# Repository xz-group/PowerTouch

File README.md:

# PowerTouch

A Genetic Algorithm-based framework that can automatically generate `wired ghost touch attacks` given security objectives (e.g., types and locations of desired ghost touches).

## About this work

For more details, please refer to our **ICCAD'22** paper: [_PowerTouch: A Security Objective-Guided Automation Framework
for Generating Wired Ghost Touch Attacks on Touchscreens_](ICCAD2022_PowerTouch.pdf).

## Dependencies

### Software Dependencies

* Standard packages: `ctypes`, `numpy`, `re`, `datetime`, `pandas`, `warnings`, `matplotlib`, `statistics`, `time`

* Python Genetic Algorithm Library: [PyGAD](https://pygad.readthedocs.io/en/latest/)
  ```bash
  pip install pygad
  ```

* Android Debug Bridge (ADB): [Android SDK Platform Tools](https://developer.android.com/studio/releases/platform-tools).
  > Currently, the framework only supports Android devices. We will add support for iOS devices in the future.

* Clone this repository
  ```bash
  git clone https://github.com/xz-group/PowerTouch.git
  ```

### Hardware Dependencies

* `All-in-one USB instrument`: [Analog Discovery 2](https://digilent.com/shop/analog-discovery-2-100ms-s-usb-oscilloscope-logic-analyzer-and-variable-power-supply/) 
with [BNC Adapter board](https://digilent.com/shop/bnc-adapter-for-analog-discovery/).

  * Five instruments are implemented in Analog Discovery 2 for this framework: 
    * `oscilloscope`: to capture the TX excitation signal of the touchscreen and monitor the generated noise signal.
    * `waveform generator`: to generate the noise signal.
    * `pattern generator`: to generate digital control signals for the relays on the customized noise injection PCB.
    * `logic analyzer`: to monitor the above digital control signals.
    * `power supply`: to power the customized noise injection PCB.

* `High-voltage amplifier module`: we use [MX200 Piezo Driver](https://www.piezodrive.com/modules/mx200-high-performance-piezo-driver/) for this project.
  But any high-voltage amplifier module that can generate minimum 60Vpp signal with 500kHz bandwidth should work.
  >   The bandwidth of MX200 is 200KHz also. We extend the bandwidth to around 500KHz by calibrating the gain of the amplifier. See [here]() for details.

* Our `customized noise injection PCB`: source design files are available in [hardware](./hardware) folder.
  
  * The board is powered by 5V through `5V` and `GND` pins. 
  * It contains four RF relay ([9814-500 relay](https://www.digikey.com/en/products/detail/coto-technology/9814-05-00/586522)) channels: CH1, CH2, CH3, and CH4.
    * `CH1` is used to capture the TX excitation signal of the touchscreen. It is connected to the `SHIELD` of USB connector.
    * `CH2` is used to inject high-voltage noise signal to the touchscreen. It is connected to the `SHIELD` of USB connector.
    * `CH3` and `CH4` are used to charge the smartphone when conducting the experiments. They are connected to the `VBUS` and `VGND` of USB connector, respectively.
  * The relays are controlled through `EN_CH1`, `EN_CH2`, `EN_CH3`, `EN_CH4` pins, respectively. High enables (>=3.3V) the relays, and low disables the relays.
  * `CH1` and `CH2` are connected outside the PCB through `BNC` connectors. The `SMA` connectors. `SHIELD` is connected outside the PCB through `BNC` connectors. 

* `Power supply`: this is used to power the high-voltage amplifier module and charge the smartphone (if enable charging the phone feature). We use [Keithley 2231A-30-3 Triple-channel DC Power Supply](https://www.tek.com/en/products/keithley/dc-power-supplies/2220-2230-2231-series).

* `Metal sheet`: to be connected to the `EARTH` of the wall outlet. This is used to build the true ground plane for converting the noise from differential mode to common mode.
We use [this one](https://a.co/d/iU6o7kK) for this project.

## How to Use

Please refer to the example usage code in `PowerTouch/example_usage_code` folder for details.

## Citation

If you use this framework for your research, please cite our [ICCAD'22 paper](ICCAD2022_PowerTouch.pdf):

```
@inproceedings{zhu2022powertouch,
  title={PowerTouch: A Security Objective-Guided Automation Framework for Generating Wired Ghost Touch Attacks on Touchscreens},
  author={Zhu, Huifeng and Yu, Zhiyuan and Cao, Weidong and Zhang, Ning and Zhang, Xuan},
  booktitle={Proceedings of the 41st IEEE/ACM International Conference on Computer-Aided Design},
  pages={1--9},
  year={2022}
}
```

## Contact Information

If you have any questions regarding using this framework, please feel free to contact us at [zhuhuifeng@wustl.edu](mailto:zhuhuifeng@wustl.edu).

## Roadmap
- [ ] To be updated

## Version History

* 0.1
  * Initial Release

## License

This framework is licensed under the `GNU3` License - see the [LICENSE.md](LICENSE) file for details

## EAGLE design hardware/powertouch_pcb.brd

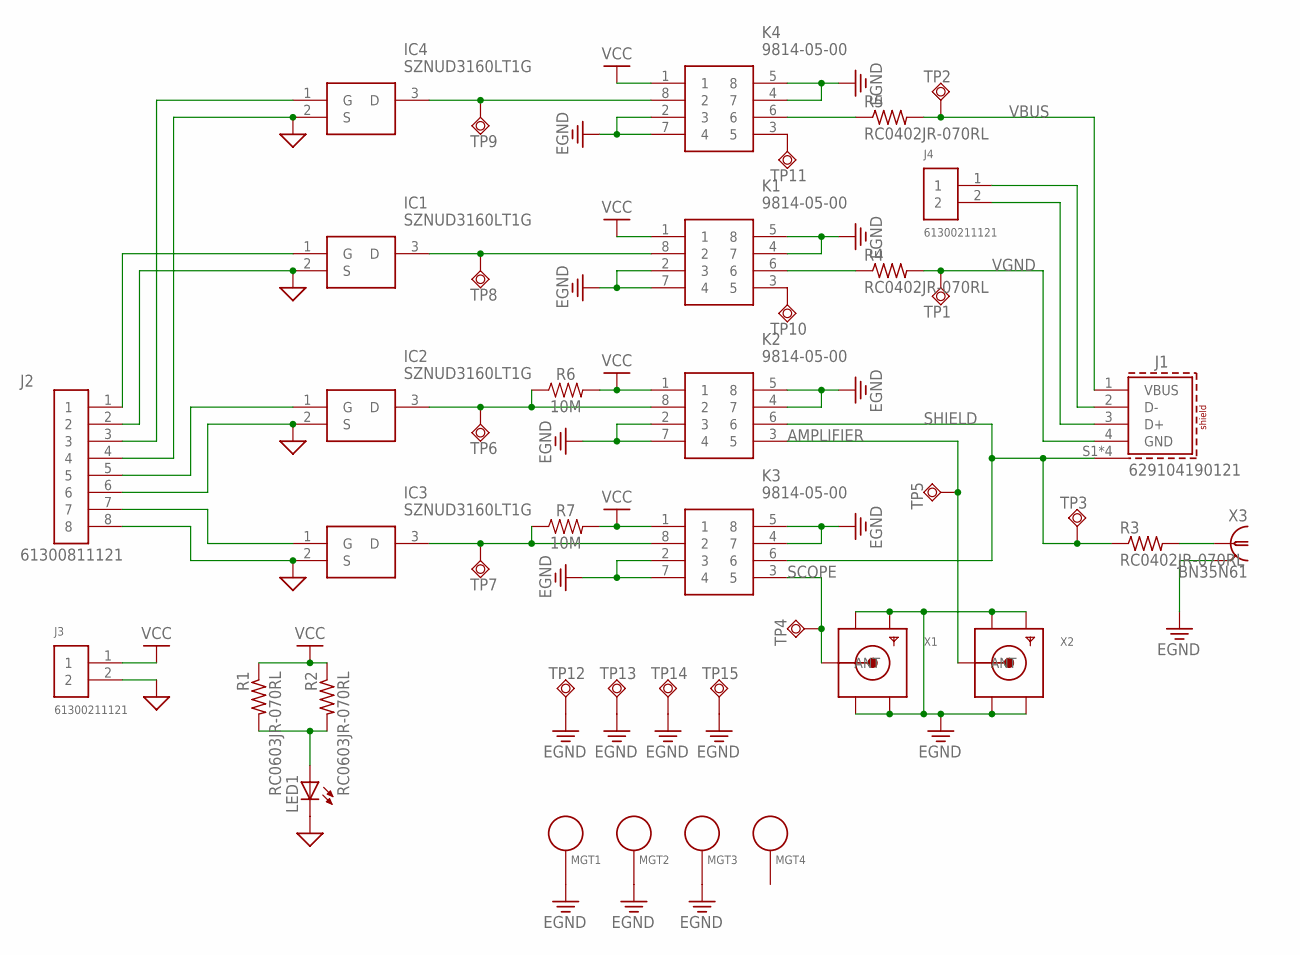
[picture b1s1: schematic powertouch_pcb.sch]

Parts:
IC1, IC2, IC3, IC4: SZNUD3160LT1G; SOT96P237X111-3N
J1: 629104190121
J2: 61300811121
J3, J4: 61300211121
K1, K2, K3, K4: 9814-05-00; SOP102P1295X457-8N
LED1: LEDCHIPLED_0603; CHIPLED_0603
MGT1, MGT2, MGT3, MGT4: BEAGLEBONEBLACK_MOUNTING_HOLE
R1, R2: RC0603JR-070RL; RES_0603
R3, R4, R5: RC0402JR-070RL; RES_0402
R6, R7: 10M; AXIAL-0.3
TP1, TP2, TP3, TP4, TP5, TP10, TP11, TP12, TP13, TP14, TP15: TESTPAD_TPSQPAD1-13; TESTPAD_P1-13
TP6, TP7, TP8, TP9: TESTPAD_TPSQTP07SQ; TESTPAD_TP07SQ
X1, X2: SMACONNECTOR_EDGE; SMA_EDGELAUNCH
X3: BN35N61; B35N61

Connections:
AMPLIFIER: K2.3 (5), TP5.TP, X2.P (ANT)
EGND: K1.2 (3), K1.4 (7), K1.5 (8), K1.7 (4), K2.2 (3), K2.4 (7), K2.5 (8), K2.7 (4), K3.2 (3), K3.4 (7), K3.5 (8), K3.7 (4), K4.2 (3), K4.4 (7), K4.5 (8), K4.7 (4), MGT1.P$1, MGT2.P$1, MGT3.P$1, TP12.TP, TP13.TP, TP14.TP, TP15.TP, X1.GND@1 (GND4), X1.GND@2 (GND3), X1.GND@3 (GND2), X1.GND@4 (GND1), X2.GND@1 (GND4), X2.GND@2 (GND3), X2.GND@3 (GND2), X2.GND@4 (GND1), X3.2, X3.3 (2), X3.4 (2), X3.5 (2)
GND: IC1.2 (S), IC2.2 (S), IC3.2 (S), IC4.2 (S), J2.2, J2.4, J2.6, J2.8, J3.2, LED1.C
unnamed: K1.3 (5), TP10.TP
unnamed: K4.3 (5), TP11.TP
unnamed: IC3.3 (D), K3.8 (2), R7.P$1 (1), TP7.TP
unnamed: IC2.3 (D), K2.8 (2), R6.P$1 (1), TP6.TP
unnamed: IC3.1 (G), J2.7
unnamed: IC4.3 (D), K4.8 (2), TP9.TP
unnamed: IC2.1 (G), J2.5
unnamed: IC1.3 (D), K1.8 (2), TP8.TP
unnamed: IC1.1 (G), J2.1
unnamed: J1.3 (D+), J4.2
unnamed: IC4.1 (G), J2.3
unnamed: J1.2 (D-), J4.1
unnamed: LED1.A, R1.2, R2.2
unnamed: K1.6, R4.1
unnamed: K4.6, R5.1
unnamed: R3.2, X3.1
SCOPE: K3.3 (5), TP4.TP, X1.P (ANT)
SHIELD: J1.S1 (SHIELD), J1.S2 (SHIELD), J1.S3 (SHIELD), J1.S4 (SHIELD), K2.6, K3.6, R3.1, TP3.TP
VBUS: J1.1 (VBUS), R5.2, TP2.TP
VCC: J3.1, K1.1, K2.1, K3.1, K4.1, R1.1, R2.1, R6.P$2 (2), R7.P$2 (2)
VGND: J1.4 (GND), R4.2, TP1.TP

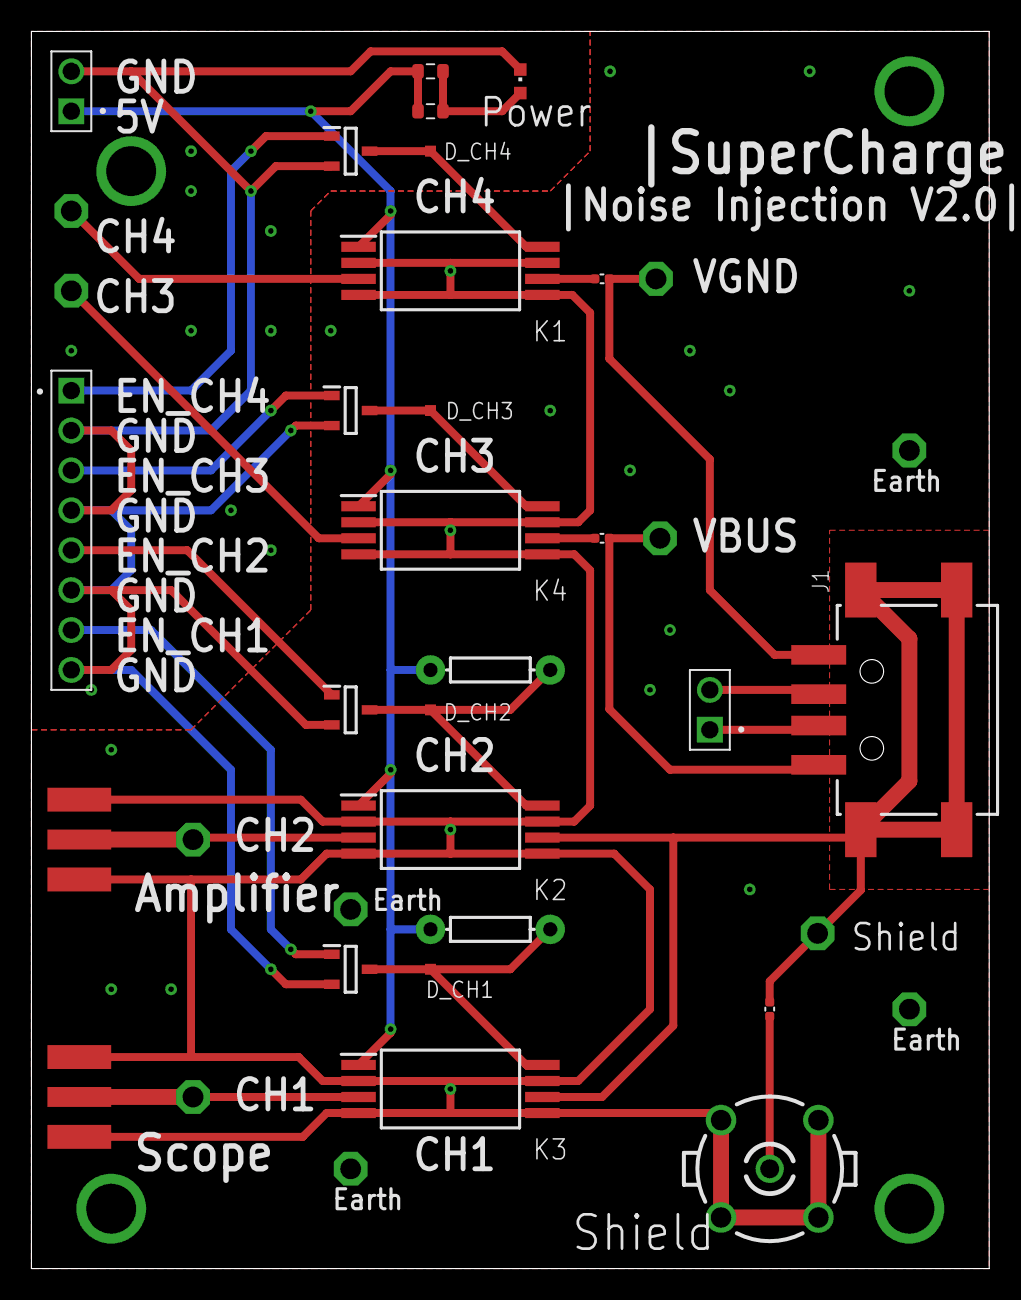
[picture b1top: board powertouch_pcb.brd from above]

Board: 2 copper layers, 61.0 x 78.7 mm, 42 parts (0 on the bottom side), 24 nets.

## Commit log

2022-09-19 Initial release
2022-09-19 Update hardware design files
2022-09-19 Update codes and results
2023-06-22 Update software

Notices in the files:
parts and their libraries:
Wurth_Connectors_WR-USB: Copyright: Würth Elektronik
SparkFun-Resistors: Licensing: Creative Commons ShareAlike 4.0 International - https://creativecommons.org/licenses/by-sa/4.0
